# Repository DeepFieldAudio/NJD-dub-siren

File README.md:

Hello!

All you have here is the work on wich i spent countless hours and that i'm really happy to share with you.
If you are about to make your own version of this preamp, please share it Under the same conditions as i did.
Also, if you happen to discover mistakes that i made, or ways to improve the design, or you just built your own NJD,
then please share it with me and the rest of the world. I would love to see your builds!!

NJD V1 DOC.pdf is the complete documentation, it includes schematic, BOM, details of the pcb, wiring diagram,
and a buying list allowing you to directly access a basket at tme.eu.
GERBER NJD V1.zip is the file you need to upload on the website of the pcb manufacturer of your choice to get the pcb built.
ibom.html is an interactive bom, making it easier to build the pcb
you will also find all the kicad files that you can use to make your own mods of the design

contact me at deep field audio on instagram and facebook

this work shall remain open source and free.

Nélo Breuiller

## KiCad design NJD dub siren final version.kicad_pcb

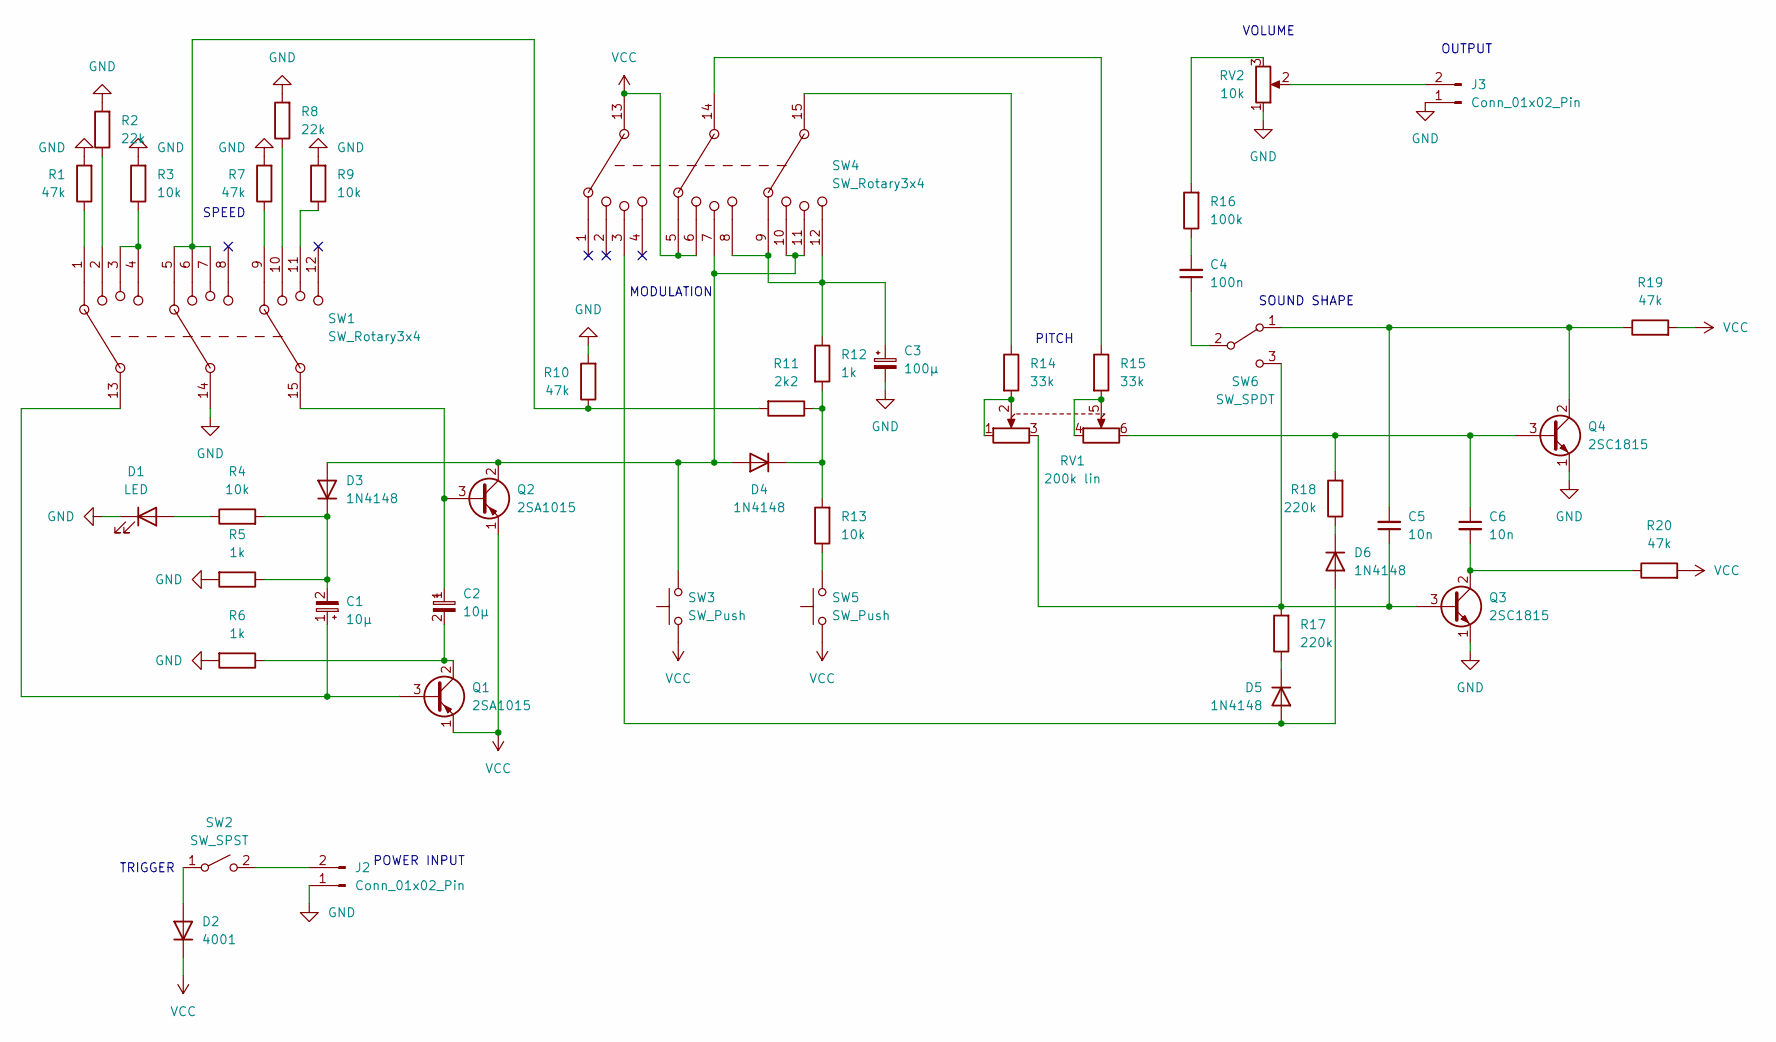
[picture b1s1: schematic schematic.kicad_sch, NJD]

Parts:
C1, C2: 10µ; CP_Radial_D5.0mm_P2.50mm
C3: 100µ; CP_Radial_D5.0mm_P2.50mm
C4: 100n; C_Rect_L7.2mm_W2.5mm_P5.00mm_FKS2_FKP2_MKS2_MKP2
C5, C6: 10n; C_Rect_L7.2mm_W2.5mm_P5.00mm_FKS2_FKP2_MKS2_MKP2
D1: LED; LED_D5.0mm
D2: 4001; D_DO-35_SOD27_P7.62mm_Horizontal
D3, D4, D5, D6: 1N4148; D_DO-35_SOD27_P7.62mm_Horizontal
J2, J3: Conn_01x02_Pin; SolderWire-0.15sqmm_1x02_P4mm_D0.5mm_OD1.5mm
Q1, Q2: 2SA1015; TO-92_Inline_Wide
Q3, Q4: 2SC1815; TO-92_Inline_Wide
R1, R7, R10, R19, R20: 47k; R_Axial_DIN0204_L3.6mm_D1.6mm_P7.62mm_Horizontal
R2, R8: 22k; R_Axial_DIN0204_L3.6mm_D1.6mm_P7.62mm_Horizontal
R3, R4, R9, R13: 10k; R_Axial_DIN0204_L3.6mm_D1.6mm_P7.62mm_Horizontal
R5, R6, R12: 1k; R_Axial_DIN0204_L3.6mm_D1.6mm_P7.62mm_Horizontal
R11: 2k2; R_Axial_DIN0204_L3.6mm_D1.6mm_P7.62mm_Horizontal
R14, R15: 33k; R_Axial_DIN0204_L3.6mm_D1.6mm_P7.62mm_Horizontal
R16: 100k; R_Axial_DIN0204_L3.6mm_D1.6mm_P7.62mm_Horizontal
R17, R18: 220k; R_Axial_DIN0204_L3.6mm_D1.6mm_P7.62mm_Horizontal
RV1: 200k lin; SolderWire-0.25sqmm_1x06_P4.2mm_D0.65mm_OD1.7mm
RV2: 10k; SolderWire-0.25sqmm_1x03_P4.2mm_D0.65mm_OD1.7mm
SW1, SW4: SW_Rotary3x4; 3P4T rotary switch
SW2: SW_SPST; SolderWire-0.25sqmm_1x02_P4.2mm_D0.65mm_OD1.7mm
SW3, SW5: SW_Push; SolderWire-0.25sqmm_1x02_P4.2mm_D0.65mm_OD1.7mm
SW6: SW_SPDT; SolderWire-0.25sqmm_1x03_P4.2mm_D0.65mm_OD1.7mm

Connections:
GND: C3.2, D1.1 (K), J2.1, J3.1, Q3.1 (E), Q4.1 (E), R1.2, R2.2, R3.2, R5.2, R6.2, R7.2, R8.2, R9.2, R10.2, RV2.1, SW1.14
unnamed: C3.1, R12.1, SW4.8, SW4.9, SW4.12
unnamed: C4.2, R16.1
unnamed: D1.2 (A), R4.1
unnamed: D2.2 (A), SW2.1 (A)
unnamed: D3.2 (A), D4.2 (A), Q2.2 (C), SW3.2, SW4.7, SW4.10, SW4.11
unnamed: C1.2, D3.1 (K), R4.2, R5.1
unnamed: D4.1 (K), R11.1, R12.2, R13.2
unnamed: D5.2 (A), D6.2 (A), SW4.3
unnamed: D5.1 (K), R17.1
unnamed: D6.1 (K), R18.1
unnamed: J2.2, SW2.2 (B)
unnamed: J3.2, RV2.2
unnamed: C1.1, Q1.3 (B), SW1.13
unnamed: C2.2, Q1.2 (C), R6.1
unnamed: C2.1, Q2.3 (B), SW1.15
unnamed: C5.1, Q3.3 (B), R17.2, RV1.3, SW6.3 (C)
unnamed: C6.2, Q3.2 (C), R20.1
unnamed: C6.1, Q4.3 (B), R18.2, RV1.6
unnamed: C5.2, Q4.2 (C), R19.1, SW6.1 (A)
unnamed: R1.1, SW1.1
unnamed: R2.1, SW1.2
unnamed: R3.1, SW1.3, SW1.4
unnamed: R7.1, SW1.9
unnamed: R8.1, SW1.10
unnamed: R9.1, SW1.11
unnamed: R10.1, R11.2, SW1.5, SW1.6, SW1.7
unnamed: R13.1, SW5.2
unnamed: R14.1, SW4.15
unnamed: R14.2, RV1.1, RV1.2
unnamed: R15.1, SW4.14
unnamed: R15.2, RV1.4, RV1.5
unnamed: R16.2, RV2.3
unnamed: C4.1, SW6.2 (B)
VCC: D2.1 (K), Q1.1 (E), Q2.1 (E), R19.2, R20.2, SW3.1, SW4.5, SW4.6, SW4.13, SW5.1

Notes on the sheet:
VOLUME
PITCH
SOUND SHAPE
TRIGGER
OUTPUT
MODULATION
POWER INPUT
SPEED

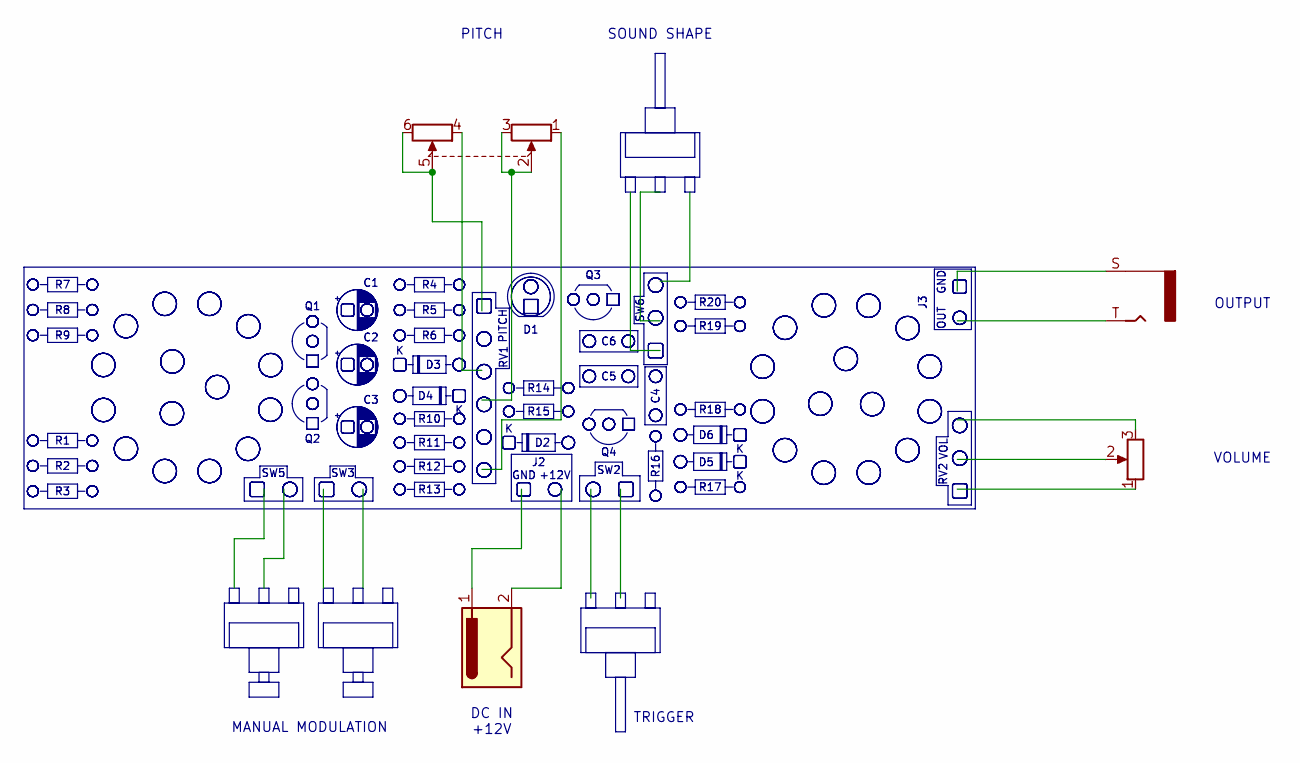
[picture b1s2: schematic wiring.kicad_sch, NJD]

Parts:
J1: AudioJack2
J4: Jack-DC
RV3: R_Potentiometer
RV4: R_Potentiometer_Dual

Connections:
unnamed: RV4.2, RV4.3
unnamed: RV4.5, RV4.6

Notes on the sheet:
PITCH
DC IN +12V
TRIGGER
MANUAL MODULATION
SOUND SHAPE
OUTPUT
VOLUME

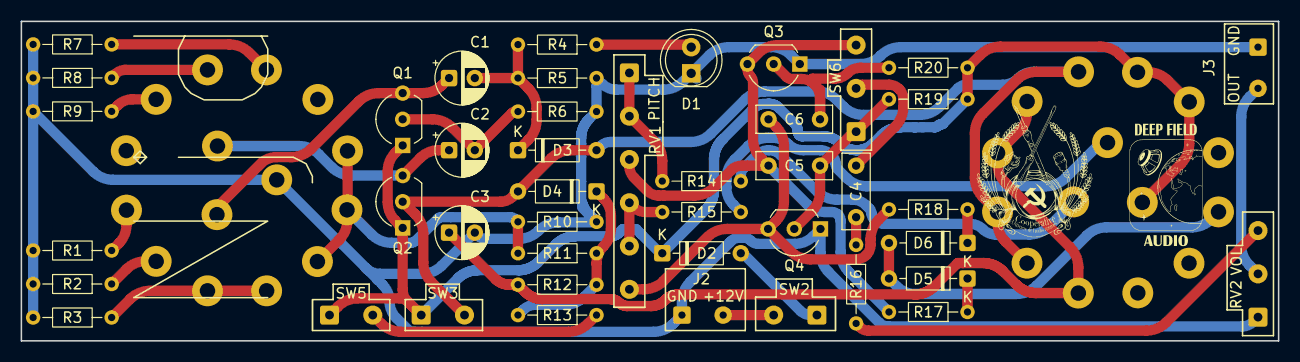
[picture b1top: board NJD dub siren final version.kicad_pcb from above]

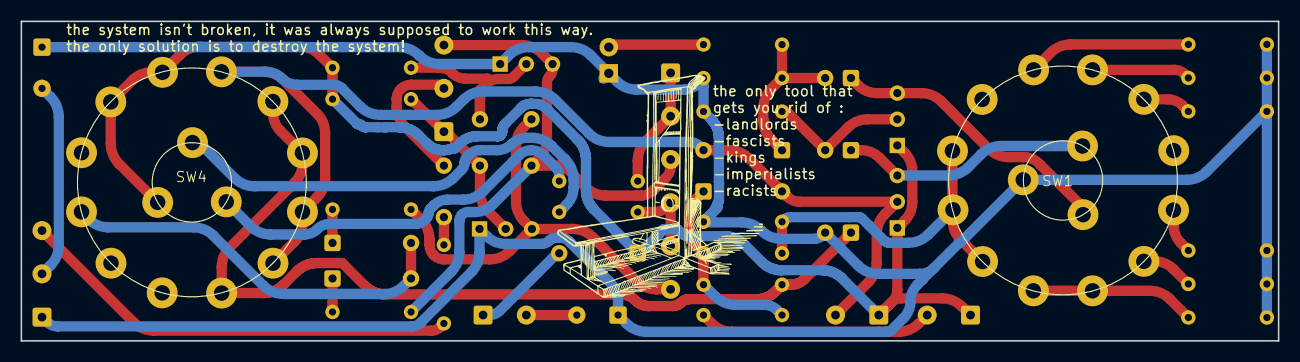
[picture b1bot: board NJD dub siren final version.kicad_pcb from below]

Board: 2 copper layers, 122.0 x 31.0 mm, 46 parts (2 on the bottom side), 35 nets.
